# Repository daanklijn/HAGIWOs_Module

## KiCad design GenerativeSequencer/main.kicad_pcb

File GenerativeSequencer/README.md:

⚠️THIS MODULE HAS NOT BEEN BUILT AND TESTED! ⚠️

⚠️ Bug found: Arduino pin 7 (D4?) and middle switch pin are not connected ⚠️

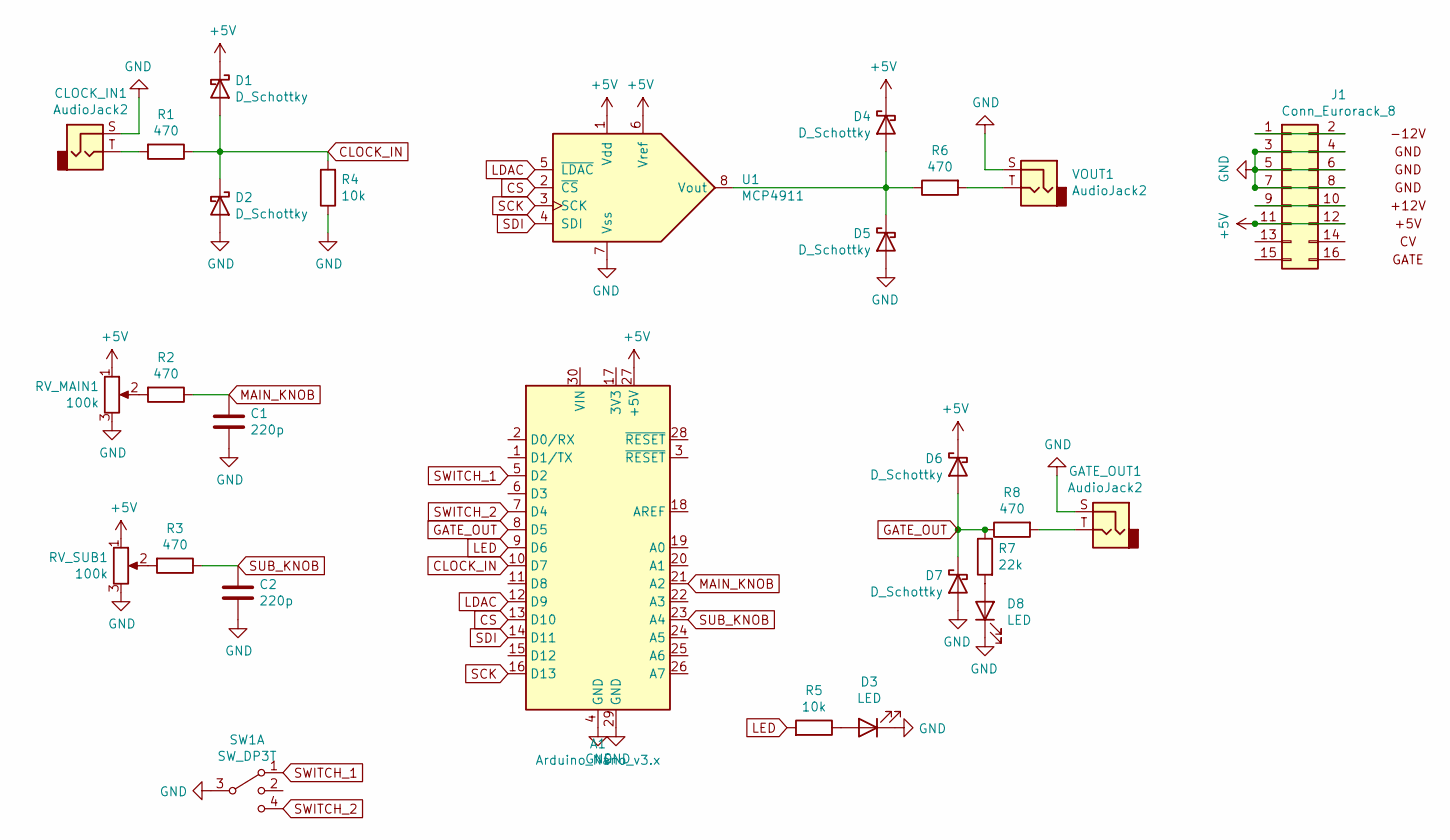
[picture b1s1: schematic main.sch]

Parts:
A1: Arduino_Nano_v3.x; Arduino_Nano
C1, C2: 220p; C_Disc_D3.4mm_W2.1mm_P2.50mm
CLOCK_IN1: AudioJack2; Jack_3.5mm_Thonkiconn_Vertical
D1, D2, D4, D5, D6, D7: D_Schottky; D_DO-35_SOD27_P7.62mm_Horizontal
D3, D8: LED; LED_DEFAULT
GATE_OUT1: AudioJack2; Jack_3.5mm_Thonkiconn_Vertical
J1: Conn_Eurorack_8; IDC-Header_2x08_Eurorack
R1, R2, R3, R6, R8: 470; R_Axial_Default
R4, R5: 10k; R_Axial_Default
R7: 22k; R_Axial_Default
RV_MAIN1: 100k; Potentiometer_Default_Vertical
RV_SUB1: 100k; Potentiometer_Default_Vertical
SW1: SW_DP3T; SW_Toggle_Blue_wSlots
U1: MCP4911; DIP-8_W7.62mm
VOUT1: AudioJack2; Jack_3.5mm_Thonkiconn_Vertical

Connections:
+5V: A1.27 (+5V), D1.1 (K), D4.1 (K), D6.1 (K), J1.11, J1.12, RV_MAIN1.1, RV_SUB1.1, U1.1 (Vdd), U1.6 (Vref)
CLOCK_IN: A1.10 (D7), D1.2 (A), D2.1 (K), R1.1, R4.2
CS: A1.13 (D10), U1.2 (~CS)
GATE_OUT: A1.8 (D5), D6.2 (A), D7.1 (K), R7.1, R8.1
GND: A1.4 (GND), A1.29 (GND), C1.2, C2.2, CLOCK_IN1.S, D2.2 (A), D3.1 (K), D5.2 (A), D7.2 (A), D8.1 (K), GATE_OUT1.S, J1.3, J1.4, J1.5, J1.6, J1.7, J1.8, R4.1, RV_MAIN1.3, RV_SUB1.3, SW1.3, U1.7 (Vss), VOUT1.S
LDAC: A1.12 (D9), U1.5 (~LDAC)
LED: A1.9 (D6), R5.2
MAIN_KNOB: A1.21 (A2), C1.1, R2.1
unnamed: CLOCK_IN1.T, R1.2
unnamed: D3.2 (A), R5.1
unnamed: D4.2 (A), D5.1 (K), R6.1, U1.8 (Vout)
unnamed: D8.2 (A), R7.2
unnamed: GATE_OUT1.T, R8.2
unnamed: J1.1, J1.2
unnamed: J1.9, J1.10
unnamed: R2.2, RV_MAIN1.2
unnamed: R3.2, RV_SUB1.2
unnamed: R6.2, VOUT1.T
SCK: A1.16 (D13), U1.3 (SCK)
SDI: A1.14 (D11), U1.4 (SDI)
SUB_KNOB: A1.23 (A4), C2.1, R3.1
SWITCH_1: A1.5 (D2), SW1.1
SWITCH_2: A1.7 (D4), SW1.4

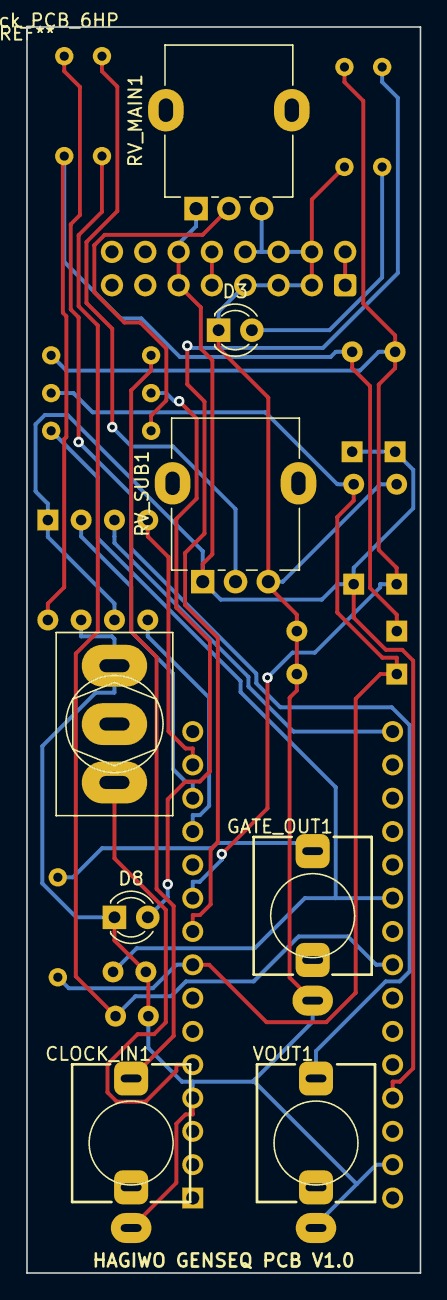
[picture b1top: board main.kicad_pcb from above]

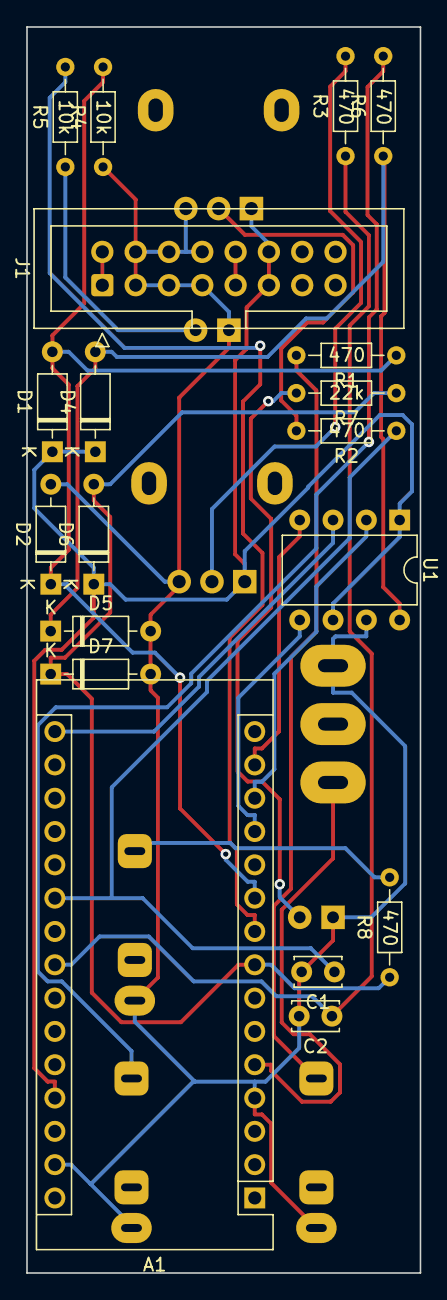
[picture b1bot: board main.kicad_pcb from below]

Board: 2 copper layers, 30.0 x 95.0 mm, 27 parts (19 on the bottom side), 22 nets.

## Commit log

2021-09-12 Add Ring mod / wave folder panel
2021-09-13 Wave&fold v1.0
2021-09-13 Add panel and gerbers
2021-10-14 Add GenSeq PCB v1.0
